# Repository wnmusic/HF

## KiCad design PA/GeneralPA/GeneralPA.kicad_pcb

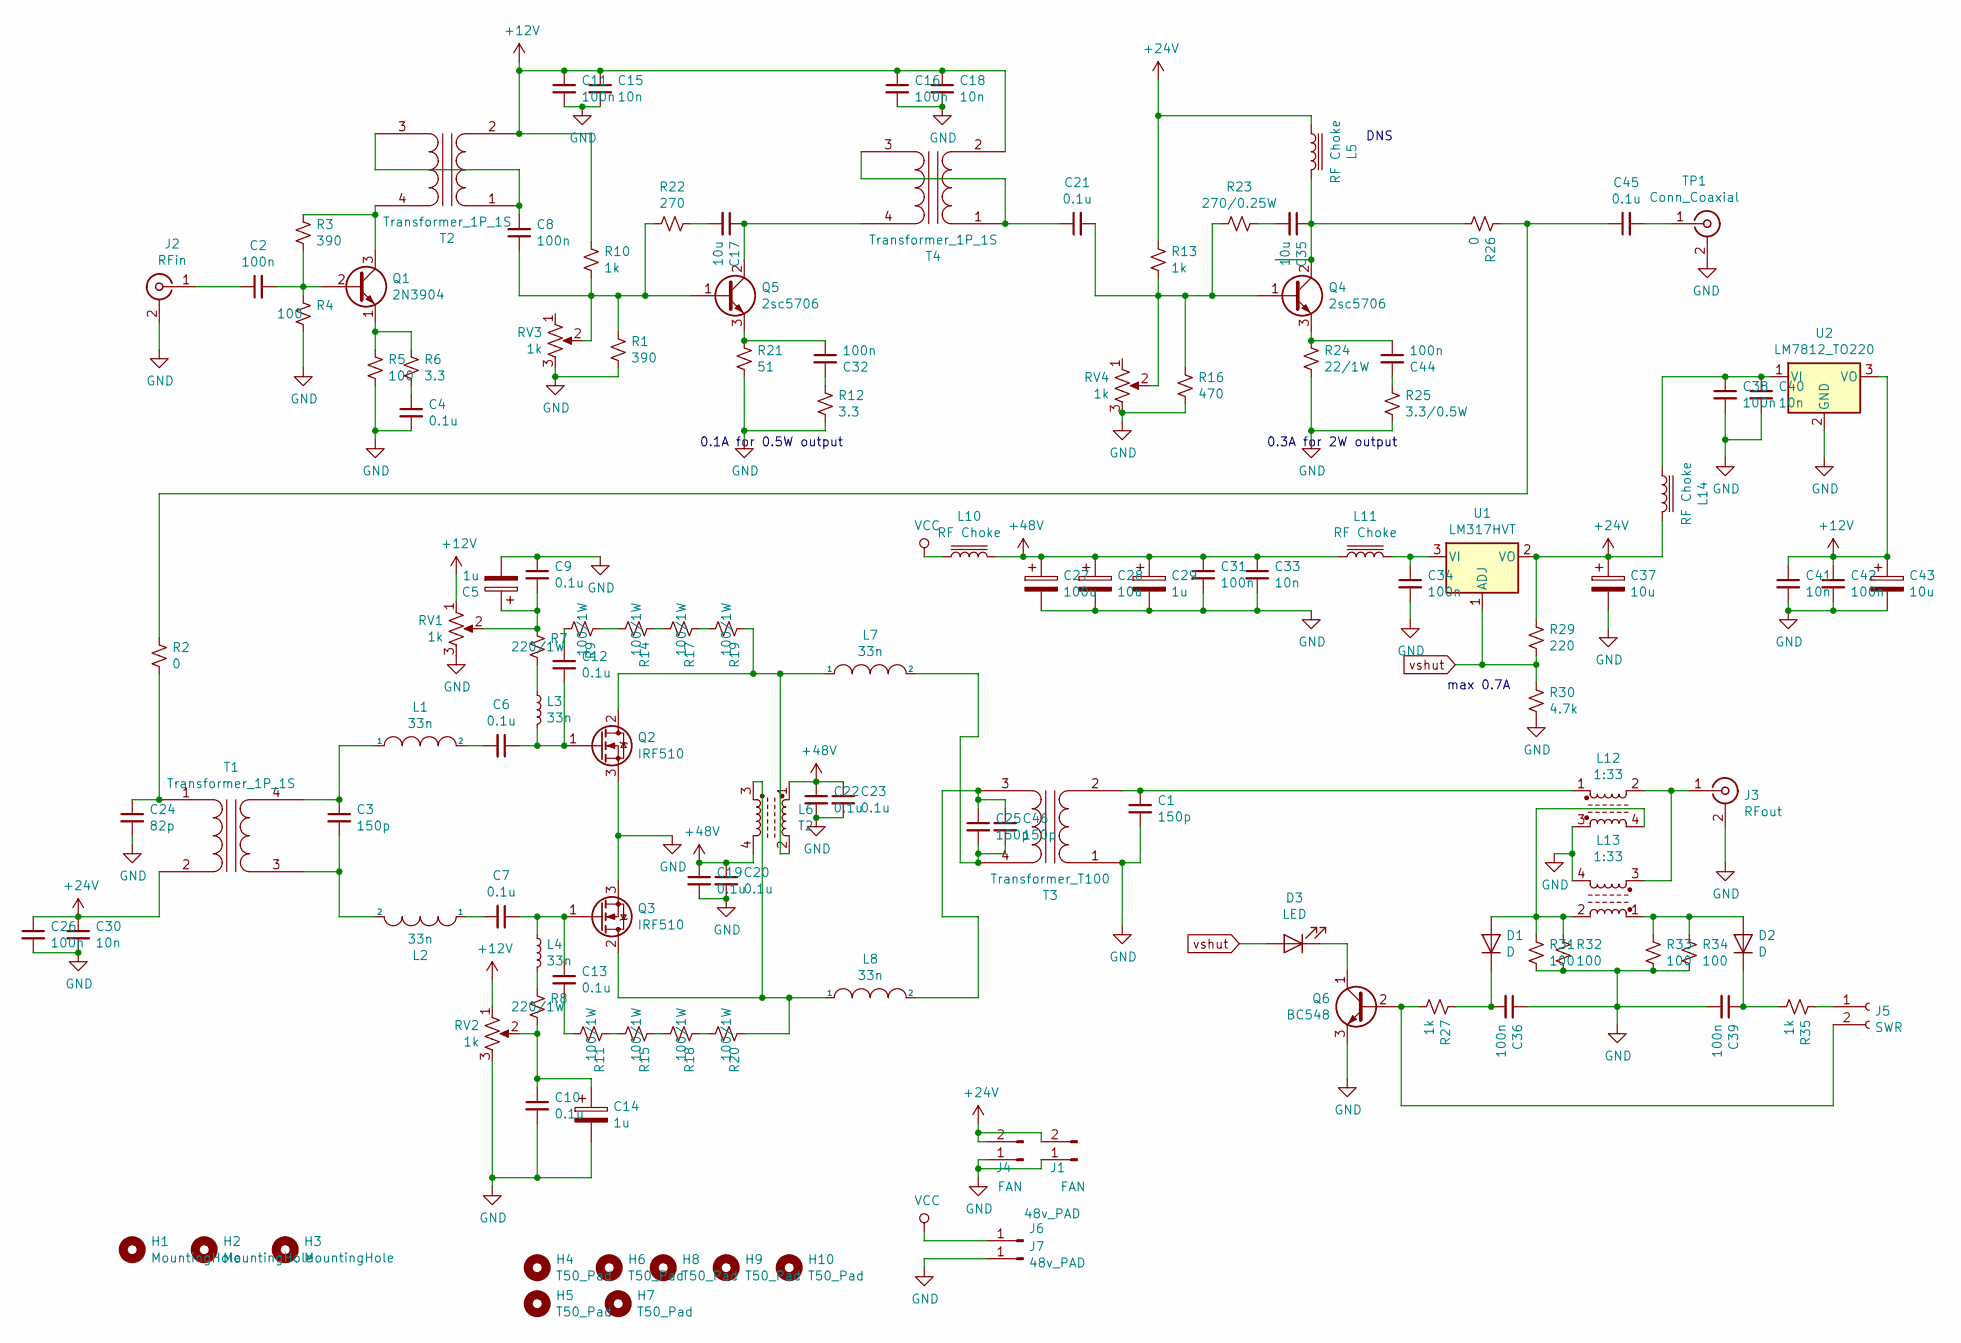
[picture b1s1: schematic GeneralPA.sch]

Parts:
C1, C25, C46: 150p; C_1206_3216Metric_Pad1.42x1.75mm_HandSolder
C2, C8, C11, C16, C26, C31, C32, C34, C36, C38, C39, C42, C44: 100n; C_0805_2012Metric_Pad1.15x1.40mm_HandSolder
C3: 150p; C_0805_2012Metric_Pad1.15x1.40mm_HandSolder
C4, C6, C7, C10, C21, C45: 0.1u; C_0805_2012Metric_Pad1.15x1.40mm_HandSolder
C5, C14, C29: 1u; CP_Radial_D5.0mm_P2.50mm
C9, C12, C13, C19, C20, C22, C23: 0.1u; C_1206_3216Metric_Pad1.42x1.75mm_HandSolder
C15, C18, C30, C33, C40, C41: 10n; C_0805_2012Metric_Pad1.15x1.40mm_HandSolder
C17, C35: 10u; C_1206_3216Metric_Pad1.42x1.75mm_HandSolder
C24: 82p; C_0805_2012Metric_Pad1.15x1.40mm_HandSolder
C27: 100u; CP_Radial_D10.0mm_P5.00mm
C28, C37, C43: 10u; CP_Radial_D5.0mm_P2.50mm
D1, D2: D; D_T-1_P10.16mm_Horizontal
D3: LED; LED_D1.8mm_W1.8mm_H2.4mm_Horizontal_O3.81mm_Z1.6mm
H1, H2, H3: MountingHole; MountingHole_3.2mm_M3_ISO14580_Pad
H4, H5, H6, H7, H8, H9, H10: T50_Pad; T50_Laminent
J1, J4: FAN; PinHeader_1x02_P2.54mm_Vertical
J2: RFin; SMA_Molex_73251-1153_EdgeMount_Horizontal
J3: RFout; SMA_Molex_73251-1153_EdgeMount_Horizontal
J5: SWR; PinHeader_1x02_P2.54mm_Vertical
J6, J7: 48v_PAD; SolderWirePad_1x01_SMD_5x10mm
L1, L2, L3, L4, L7, L8: 33n; HomeMade_L_aircore
L5, L14: RF Choke; L_Axial_L7.0mm_D3.3mm_P5.08mm_Vertical_Fastron_MICC
L6: T2; HomeMade_BalChoke
L10: RF Choke; L_Toroid_Vertical_L21.6mm_W8.4mm_P8.38mm_Pulse_G
L11: RF Choke; L_Radial_D10.0mm_P5.00mm_Fastron_07P
L12, L13: 1:33; HomeMade_T50_1t33t
Q1: 2N3904; TO-92_Inline_Wide
Q2, Q3: IRF510; TO-220-3_Horizontal_TabDown
Q4, Q5: 2sc5706; TO-252-2
Q6: BC548; TO-92_Inline_Wide
R1, R3: 390; R_0805_2012Metric_Pad1.15x1.40mm_HandSolder
R2, R26: 0; R_0815_2038Metric_Pad1.53x4.00mm_HandSolder
R4, R5, R31, R32, R33, R34: 100; R_0805_2012Metric_Pad1.15x1.40mm_HandSolder
R6, R12: 3.3; R_0805_2012Metric_Pad1.15x1.40mm_HandSolder
R7, R8: 220/1W; R_Axial_DIN0411_L9.9mm_D3.6mm_P12.70mm_Horizontal
R9, R11, R14, R15, R17, R18: 100/1W; R_Axial_DIN0411_L9.9mm_D3.6mm_P12.70mm_Horizontal
R10, R13, R27, R35: 1k; R_0805_2012Metric_Pad1.15x1.40mm_HandSolder
R16: 470; R_0805_2012Metric_Pad1.15x1.40mm_HandSolder
R19, R20: 100/1W; R_Axial_DIN0411_L9.9mm_D3.6mm_P15.24mm_Horizontal
R21: 51; R_0805_2012Metric_Pad1.15x1.40mm_HandSolder
R22: 270; R_0805_2012Metric_Pad1.15x1.40mm_HandSolder
R23: 270/0.25W; R_Axial_DIN0411_L9.9mm_D3.6mm_P12.70mm_Horizontal
R24: 22/1W; R_Axial_DIN0411_L9.9mm_D3.6mm_P12.70mm_Horizontal
R25: 3.3/0.5W; R_Axial_DIN0411_L9.9mm_D3.6mm_P12.70mm_Horizontal
R29: 220; R_0805_2012Metric_Pad1.15x1.40mm_HandSolder
R30: 4.7k; R_0805_2012Metric_Pad1.15x1.40mm_HandSolder
RV1, RV2, RV3, RV4: 1k; Potentiometer_Bourns_3266Y_Vertical
T1, T2, T4: Transformer_1P_1S; HomeMade_Transformer_T50
T3: Transformer_T100; HomeMade_Transformer_T100
TP1: Conn_Coaxial; U.FL_Molex_MCRF_73412-0110_Vertical
U1: LM317HVT; TO-220-3_Horizontal_TabDown
U2: LM7812_TO220; TO-220-3_Vertical

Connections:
+12V: C11.1, C15.1, C16.1, C18.1, C41.1, C42.1, C43.1, R10.1, RV1.1, RV2.1, T2.2 (AB), T4.2 (AB), U2.3 (VO)
+24V: C26.1, C30.1, C37.1, J1.2, J4.2, L5.1, L14.2, R13.1, R29.2, T1.2 (AB), U1.2 (VO)
+48V: C19.1, C20.1, C22.1, C23.1, C27.1, C28.1, C29.1, C31.1, C33.1, L6.1, L6.4, L10.2, L11.1
GND: C1.2, C4.2, C5.2, C9.1, C10.2, C11.2, C14.2, C15.2, C16.2, C18.2, C19.2, C20.2, C22.2, C23.2, C24.2, C26.2, C27.2, C28.2, C29.2, C30.2, C31.2, C33.2, C34.2, C36.1, C37.2, C38.2, C39.2, C40.2, C41.2, C42.2, C43.2, J1.1, J2.2 (Ext), J3.2 (Ext), J4.1, J7.1, L12.3, L13.4, Q2.3 (S), Q3.3 (S), Q6.3 (E), R1.2, R4.2, R5.2, R12.2, R16.2, R21.2, R24.2, R25.2, R30.1, R31.1, R32.1, R33.1, R34.1, RV1.3, RV2.3, RV3.3, RV4.3, T3.1 (AA), TP1.2 (Ext), U2.2 (GND)
unnamed: C1.1, L12.1, T3.2 (AB)
unnamed: C2.1, J2.1 (In)
unnamed: C2.2, Q1.2 (B), R3.2, R4.1
unnamed: C3.1, L1.1, T1.4 (SB)
unnamed: C3.2, L2.2, T1.3 (SA)
unnamed: C4.1, R6.2
unnamed: C5.1, C9.2, R7.1, RV1.2
unnamed: C6.2, L1.2
unnamed: C7.2, L2.1
unnamed: C8.1, Q5.1 (B), R1.1, R10.2, R22.1, RV3.2
unnamed: C8.2, T2.1 (AA), T2.3 (SA)
unnamed: C10.1, C14.1, R8.2, RV2.2
unnamed: C12.1, R9.2
unnamed: C6.1, C12.2, L3.2, Q2.1 (G)
unnamed: C7.1, C13.1, L4.1, Q3.1 (G)
unnamed: C13.2, R11.2
unnamed: C17.1, Q5.2 (C), T4.4 (SB)
unnamed: C17.2, R22.2
unnamed: C21.1, T4.1 (AA), T4.3 (SA)
unnamed: C21.2, Q4.1 (B), R13.2, R16.1, R23.1, RV4.2
unnamed: C24.1, R2.1, T1.1 (AA)
unnamed: C25.1, C46.1, L8.2, T3.3 (SA)
unnamed: C25.2, C46.2, L7.2, T3.4 (SB)
unnamed: C32.1, Q5.3 (E), R21.1
unnamed: C32.2, R12.1
unnamed: C34.1, L11.2, U1.3 (VI)
unnamed: C35.1, L5.2, Q4.2 (C), R26.1
unnamed: C35.2, R23.2
unnamed: C36.2, D1.1 (K), R27.2
unnamed: C38.1, C40.1, L14.1, U2.1 (VI)
unnamed: C39.1, D2.1 (K), R35.1
unnamed: C44.1, Q4.3 (E), R24.1
unnamed: C44.2, R25.1
unnamed: C45.1, R2.2, R26.2
unnamed: C45.2, TP1.1 (In)
unnamed: D1.2 (A), L12.4, L13.2, R31.2, R32.2
unnamed: D2.2 (A), L13.1, R33.2, R34.2
unnamed: D3.1 (K), Q6.1 (C)
unnamed: J3.1 (In), L12.2, L13.3
unnamed: J5.1, R35.2
unnamed: J5.2, Q6.2 (B), R27.1
unnamed: L3.1, R7.2
unnamed: L4.2, R8.1
unnamed: L6.2, L7.1, Q2.2 (D), R19.1
unnamed: L6.3, L8.1, Q3.2 (D), R20.1
unnamed: Q1.1 (E), R5.1, R6.1
unnamed: Q1.3 (C), R3.1, T2.4 (SB)
unnamed: R11.1, R15.2
unnamed: R14.1, R17.2
unnamed: R9.1, R14.2
unnamed: R15.1, R18.2
unnamed: R17.1, R19.2
unnamed: R18.1, R20.2
VCC: J6.1, L10.1
vshut: D3.2 (A), R29.1, R30.2, U1.1 (ADJ)

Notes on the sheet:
max 0.7A
0.1A for 0.5W output
0.3A for 2W output
DNS

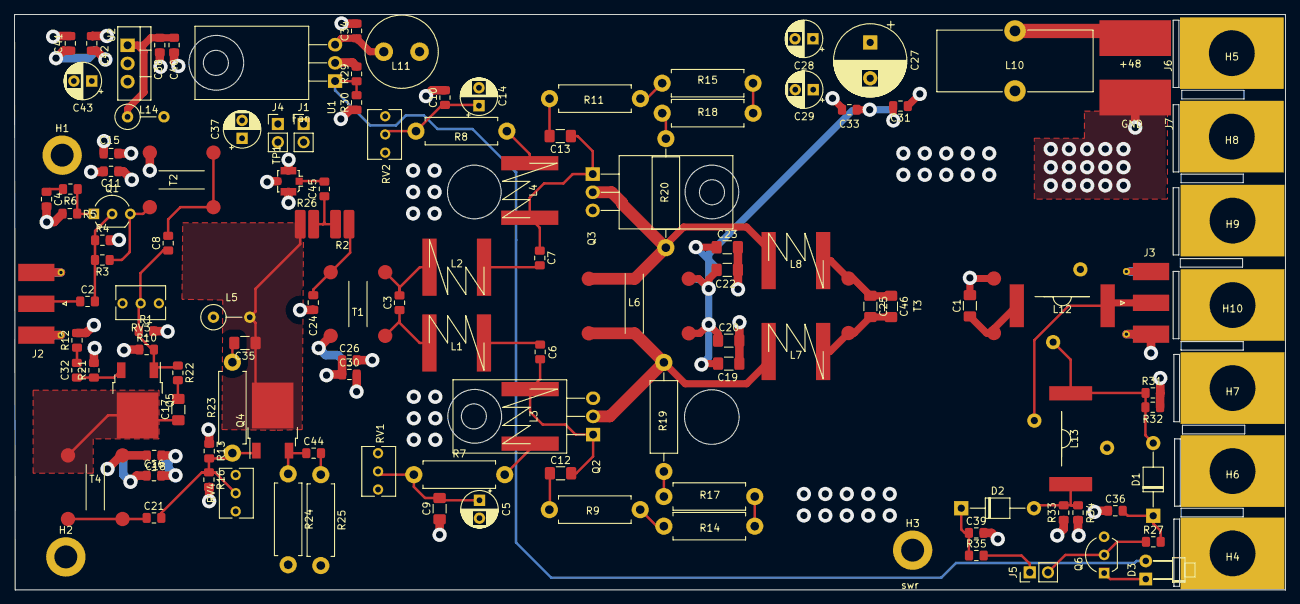
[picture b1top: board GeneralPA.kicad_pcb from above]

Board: 4 copper layers, 177.6 x 80.4 mm, 130 parts (0 on the bottom side), 59 nets.

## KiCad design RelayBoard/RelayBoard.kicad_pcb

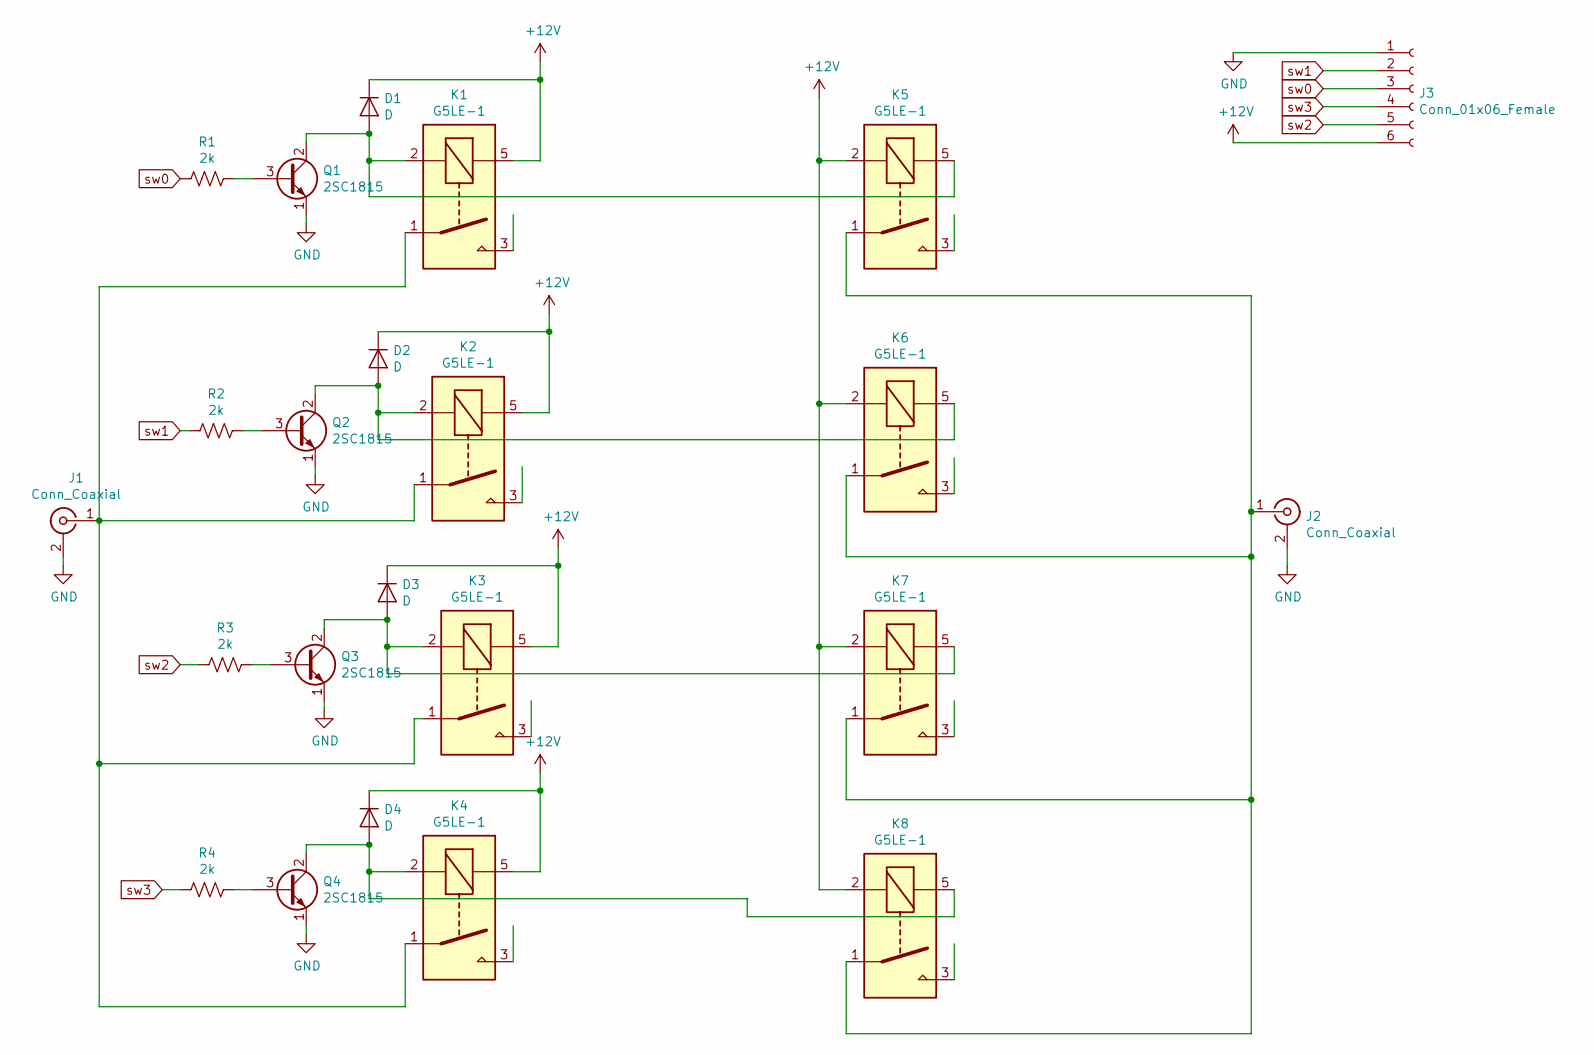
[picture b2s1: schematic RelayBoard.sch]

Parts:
D1, D2, D3, D4: D; D_T-1_P10.16mm_Horizontal
J1, J2: Conn_Coaxial; SMA_Amphenol_132289_EdgeMount
J3: Conn_01x06_Female; PinHeader_1x06_P2.54mm_Vertical
K1, K2, K3, K4, K5, K6, K7, K8: G5LE-1; Relay_SPST_Omron-G5LE
Q1, Q2, Q3, Q4: 2SC1815; TO-92_Inline_Wide
R1, R2, R3, R4: 2k; R_0805_2012Metric_Pad1.15x1.40mm_HandSolder

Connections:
+12V: D1.1 (K), D2.1 (K), D3.1 (K), D4.1 (K), J3.6, K1.5, K2.5, K3.5, K4.5, K5.2, K6.2, K7.2, K8.2
GND: J1.2 (Ext), J2.2 (Ext), J3.1, Q1.1 (E), Q2.1 (E), Q3.1 (E), Q4.1 (E)
unnamed: D1.2 (A), K1.2, K5.5, Q1.2 (C)
unnamed: D2.2 (A), K2.2, K6.5, Q2.2 (C)
unnamed: D3.2 (A), K3.2, K7.5, Q3.2 (C)
unnamed: D4.2 (A), K4.2, K8.5, Q4.2 (C)
unnamed: J1.1 (In), K1.1, K2.1, K3.1, K4.1
unnamed: J2.1 (In), K5.1, K6.1, K7.1, K8.1
unnamed: Q1.3 (B), R1.1
unnamed: Q2.3 (B), R2.1
unnamed: Q3.3 (B), R3.1
unnamed: Q4.3 (B), R4.1
sw0: J3.3, R1.2
sw1: J3.2, R2.2
sw2: J3.5, R3.2
sw3: J3.4, R4.2

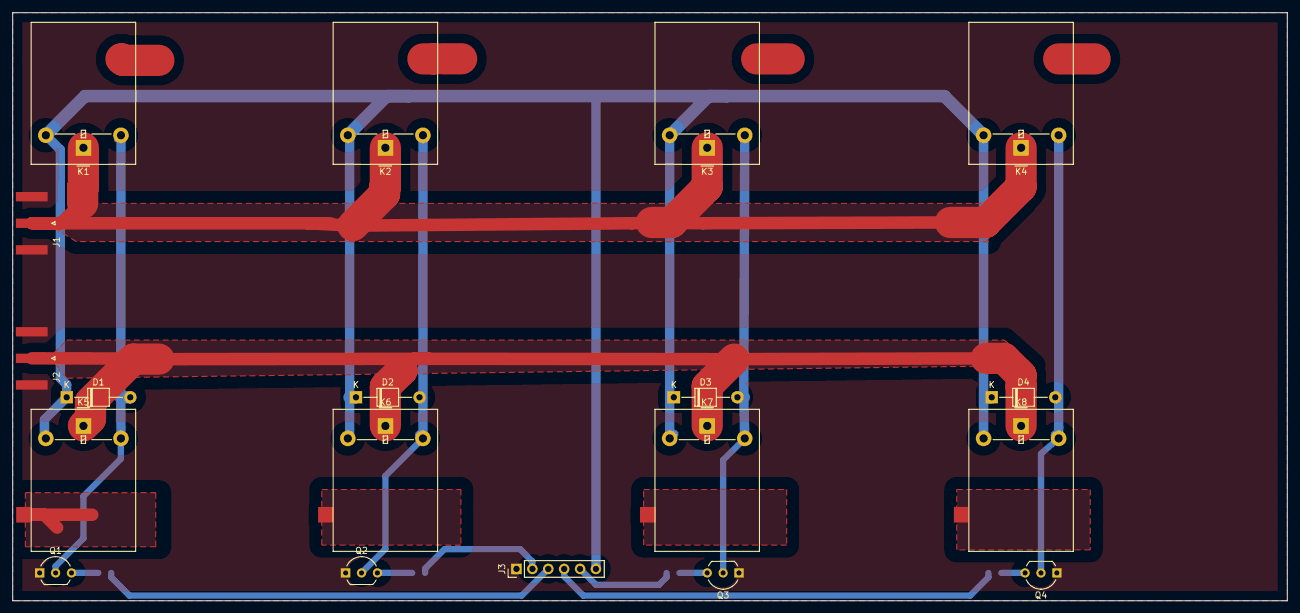
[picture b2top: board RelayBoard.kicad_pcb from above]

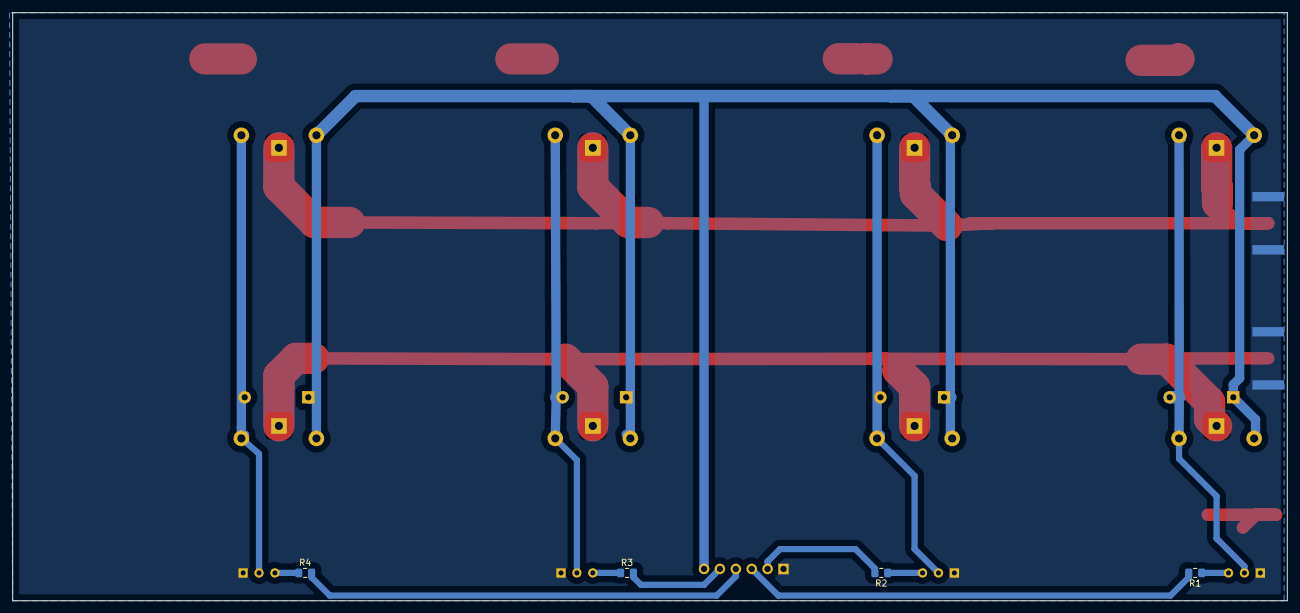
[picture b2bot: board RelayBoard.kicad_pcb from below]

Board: 2 copper layers, 203.7 x 94.0 mm, 23 parts (4 on the bottom side), 16 nets.

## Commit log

2022-05-29 Add premap
2022-05-29 add spice model
2022-06-07 study change
2022-06-07 temp change
2022-06-11 modify the feedback
2022-06-22 add input amplifier
2022-06-22 add lpf
2022-06-24 adding software directory
2022-06-25 add imgui submodule
2022-06-25 add libdsp
2022-06-29 make waterfall working
2022-06-30 push in some test
2022-07-03 add PortAudio sink, make it almost work
2022-07-03 put tune freq into waterfall
2022-07-07 add hilbert transform, upsample filter and ssb modulator
2022-07-07 per previous comment
2022-07-08 refactor pa audio
2022-07-31 adding relay baord sch
2022-07-31 finalize the filter and put some modulator code change
2022-08-01 layout the relay borad
2022-08-16 add another trial amp,
2022-08-16 add the wrong file
2022-08-23 add amp4
2022-08-28 make the driver signle op
2022-09-01 make push-pull to increase power
2022-09-10 complete one
2022-12-04 make quite a few changes.
2023-04-21 software change on hf uhd
2023-04-21 add general PA pcb
2023-04-26 update 2nd version of PA, adding some driver ciruits
2024-02-21 add missed files
2025-09-19 add a 10dBm preamp circuit
